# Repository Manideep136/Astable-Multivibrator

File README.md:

# Astable-Multivibrator

## 📌 Project Overview

This project demonstrates an **Astable Multivibrator circuit using the NE555P timer IC**.

An astable multivibrator continuously switches between HIGH and LOW states without requiring an external trigger. The output of the 555 timer produces a continuous square-wave signal, which is used to blink an LED.

The circuit is designed and documented using **KiCad**.

---

## 🔧 Components Used

| Component | Value |
|-----------|-------|
| NE555P Timer IC | 1 |
| R1 | 1 kΩ |
| R2 | 50 kΩ |
| R3 | 330 Ω |
| C1 | 0.1 µF |
| LED | 1 |
| 2-Pin Screw Terminal | 1 |
| PWR_FLAG | 2 |
| GND | As required |

---

## ⚡ Circuit Description

The NE555P is configured in **astable mode**.

The timing components **R1, R2, and C1** determine the frequency and duty cycle of the output waveform.

The output from **Pin 3 (OUT)** of the NE555P is connected to an LED through a **330 Ω current-limiting resistor**.

When the 555 output switches HIGH and LOW continuously, the LED turns ON and OFF, producing a blinking effect.

---

## 🔌 NE555P Pin Connections

| Pin | Name | Connection |
|-----|------|------------|
| 1 | GND | Ground |
| 2 | TRIG | Connected to Pin 6 and timing capacitor |
| 3 | OUT | R3 → LED → GND |
| 4 | RST | VCC |
| 5 | CONT | Not connected |
| 6 | THRES | Connected to Pin 2 |
| 7 | DISCH | Junction of R1 and R2 |
| 8 | VCC | Positive supply |

---

## 🔗 Circuit Connections

### Power Supply

- J1 Pin 1 → VCC
- J1 Pin 2 → GND
- PWR_FLAG is connected to the VCC net.
- PWR_FLAG is connected to the GND net.

### Timing Network

- R1 = 1 kΩ
- R2 = 50 kΩ
- C1 = 0.1 µF
- R1 is connected between VCC and Pin 7.
- R2 is connected between Pin 7 and the Pins 2/6 junction.
- C1 is connected between the Pins 2/6 junction and GND.

### Output

- Pin 3 (OUT) → R3 (330 Ω)
- R3 → LED
- LED → GND

---

## 📐 Working Principle

The NE555 timer operates as an astable multivibrator by repeatedly charging and discharging the capacitor.

### Charging

The capacitor charges through:

**R1 + R2**

When the capacitor voltage reaches approximately **2/3 VCC**, the threshold comparator changes state and the discharge transistor turns ON.

### Discharging

The capacitor discharges through:

**R2**

When the capacitor voltage falls to approximately **1/3 VCC**, the output changes state again and the discharge transistor turns OFF.

This charging and discharging process repeats continuously.

As a result, Pin 3 produces a continuous square-wave output.

---

## 🧮 Frequency Calculation

For a 555 timer in astable mode:

```text
f = 1.44 / ((R1 + 2R2) × C1)

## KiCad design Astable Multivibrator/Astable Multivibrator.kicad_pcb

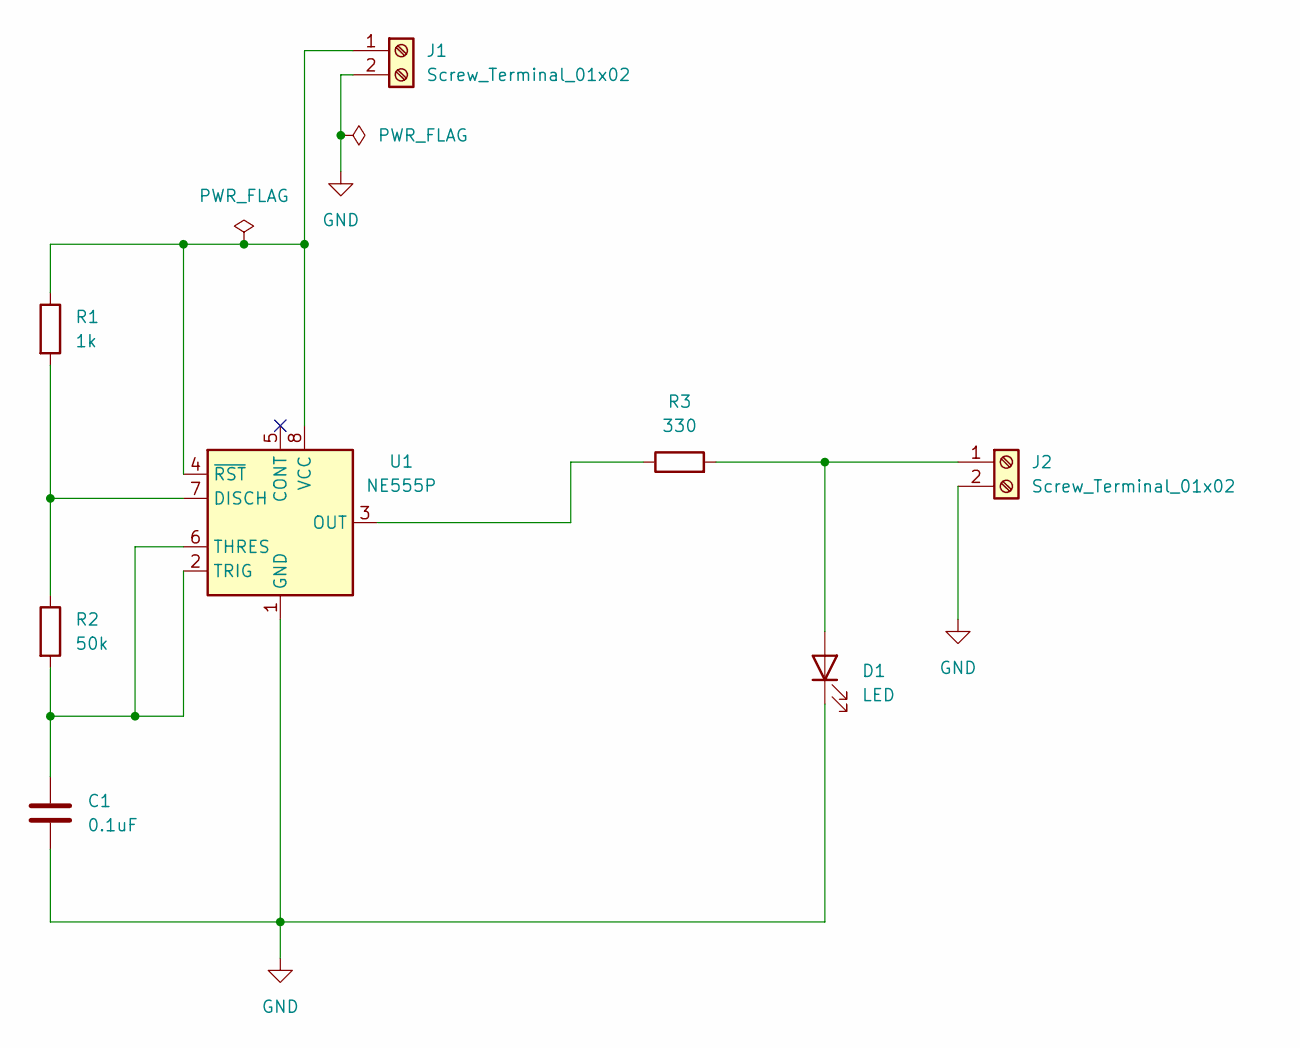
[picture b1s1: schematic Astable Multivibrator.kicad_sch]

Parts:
C1: 0.1uF; C_Disc_D3.0mm_W2.0mm_P2.50mm
D1: LED; LED_D5.0mm
J1, J2: Screw_Terminal_01x02; TerminalBlock_Phoenix_MKDS-1,5-2_1x02_P5.00mm_Horizontal
R1: 1k; R_Axial_DIN0204_L3.6mm_D1.6mm_P5.08mm_Horizontal
R2: 50k; R_Axial_DIN0204_L3.6mm_D1.6mm_P5.08mm_Horizontal
R3: 330; R_Axial_DIN0204_L3.6mm_D1.6mm_P5.08mm_Horizontal
U1: NE555P; DIP-8_W7.62mm

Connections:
GND: C1.2, D1.1 (K), J1.2, J2.2, U1.1 (GND)
unnamed: D1.2 (A), J2.1, R3.2
unnamed: J1.1, R1.1, U1.4 (~RST), U1.8 (VCC)
unnamed: R1.2, R2.1, U1.7 (DISCH)
unnamed: R3.1, U1.3 (OUT)
unnamed: C1.1, R2.2, U1.2 (TRIG), U1.6 (THRES)

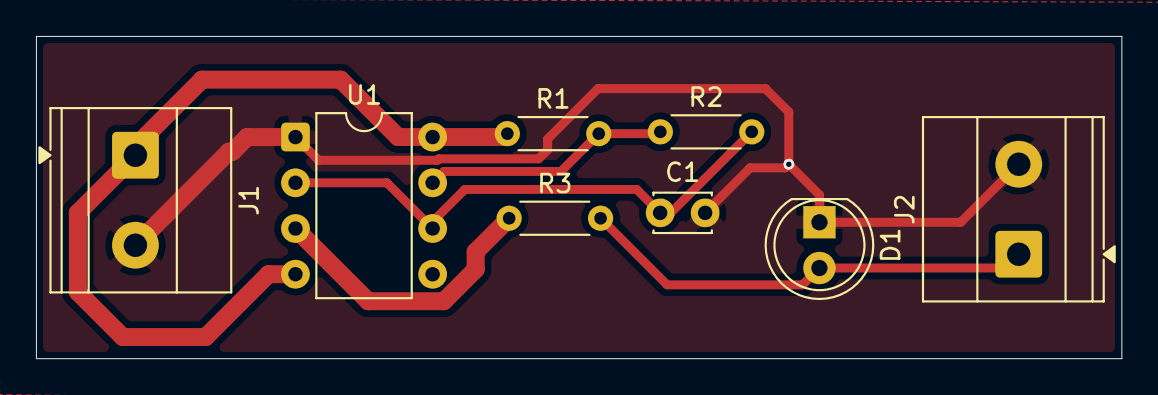
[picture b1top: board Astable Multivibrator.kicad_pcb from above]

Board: 2 copper layers, 60.3 x 17.9 mm, 8 parts (0 on the bottom side), 6 nets.
